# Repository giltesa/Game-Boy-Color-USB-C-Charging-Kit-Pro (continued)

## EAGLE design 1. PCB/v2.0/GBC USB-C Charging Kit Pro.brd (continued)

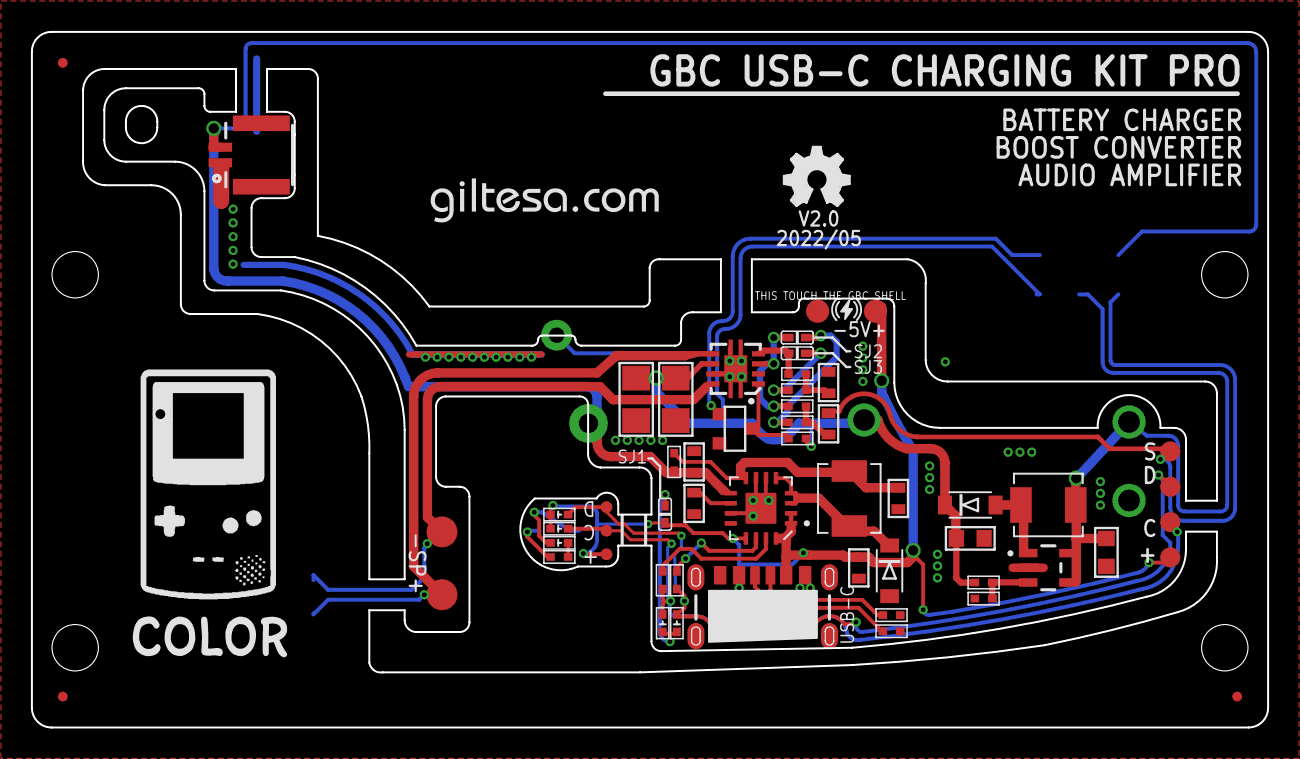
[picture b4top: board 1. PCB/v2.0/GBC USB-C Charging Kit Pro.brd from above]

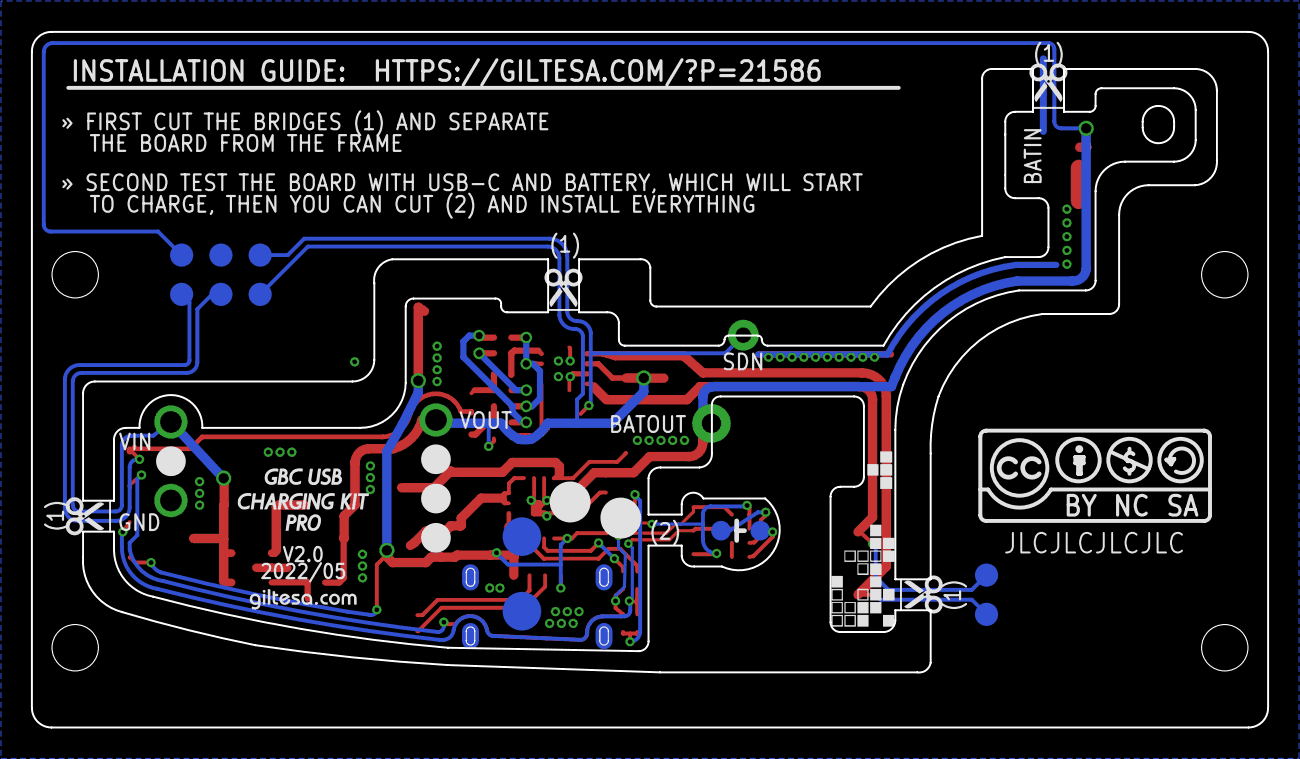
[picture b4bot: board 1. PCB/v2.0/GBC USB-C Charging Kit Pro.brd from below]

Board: 2 copper layers, 80.0 x 45.0 mm, 81 parts (17 on the bottom side), 31 nets.

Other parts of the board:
U$7: GAME_BOY_COLOR_1.2
U$8, U$13, U$14, U$15: SCISSOR
U$10: TETRIS
U$19: QI
U$28: GAME_BOY_COLOR_2
U$33: GILTESA.COM_MASK_7MM
U$34: GAME_BOY_COLOR_USB_CHARGING_KIT_PRO

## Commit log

2022-03-24 v1.0
2022-03-26 v1.1
2022-03-27 v1.1 final
2022-04-04 no message
2022-05-20 v2.0
2022-08-22 v2.2
2023-02-13 Guide updated
2023-06-18 v3.1
2023-08-03 v2.3
2024-01-04 v3.2
